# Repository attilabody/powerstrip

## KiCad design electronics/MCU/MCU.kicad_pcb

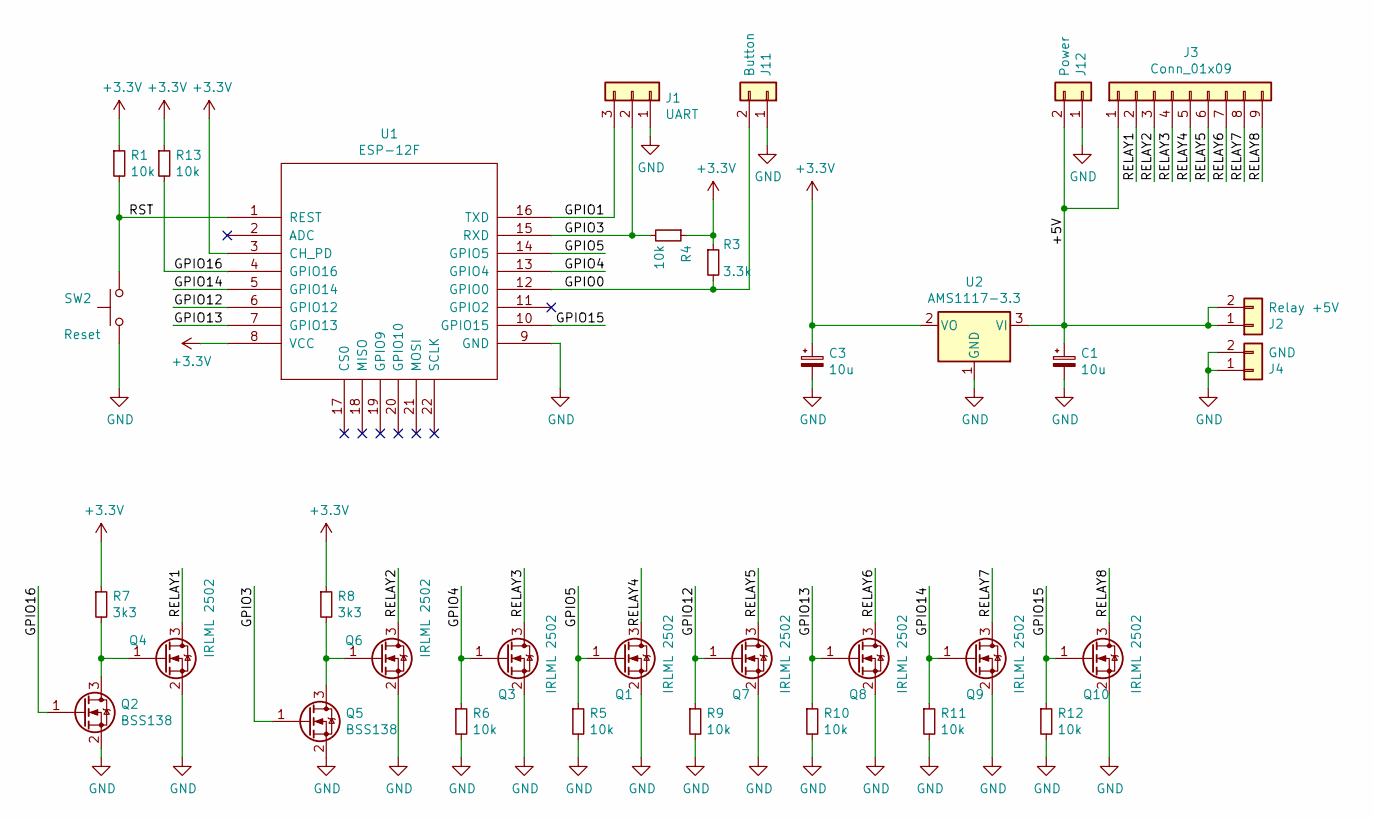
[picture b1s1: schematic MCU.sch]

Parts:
C1, C3: 10u; C_1206_3216Metric_Pad1.42x1.75mm_HandSolder
J1: UART; PinHeader_1x03_P2.54mm_Vertical
J2: Relay +5V; PinHeader_1x02_P2.54mm_Vertical
J3: Conn_01x09; PinHeader_1x09_P2.54mm_Vertical
J4: GND; PinHeader_1x02_P2.54mm_Vertical
J11: Button; JST_EH_B2B-EH-A_1x02_P2.50mm_Vertical
J12: Power; JST_EH_B2B-EH-A_1x02_P2.50mm_Vertical
Q1, Q3, Q4, Q6, Q7, Q8, Q9, Q10: IRLML 2502; SOT-23_Handsoldering
Q2, Q5: BSS138; SOT-23_Handsoldering
R1, R4, R5, R6, R9, R10, R11, R12, R13: 10k; R_0603_1608Metric_Pad1.05x0.95mm_HandSolder
R3: 3.3k; R_0603_1608Metric_Pad1.05x0.95mm_HandSolder
R7, R8: 3k3; R_0603_1608Metric_Pad1.05x0.95mm_HandSolder
SW2: Reset; SW_SPST_SKQG_WithStem
U1: ESP-12F; ESP-12E_SMD
U2: AMS1117-3.3; SOT-223-3_TabPin2

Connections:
+3V3: C3.1, R1.1, R3.1, R4.1, R7.1, R8.1, R13.1, U1.3 (CH_PD), U1.8 (VCC), U2.2 (VO)
/+5V: C1.1, J2.1, J2.2, J3.1, J12.2, U2.3 (VI); also elsewhere on the board
/GPIO0: J11.2, R3.2, U1.12 (GPIO0)
/GPIO1: J1.3, U1.16 (TXD)
/GPIO3: J1.2, Q5.1 (G), R4.2, U1.15 (RXD)
/GPIO4: Q3.1 (G), R6.1, U1.13 (GPIO4)
/GPIO5: Q1.1 (G), R5.1, U1.14 (GPIO5)
/GPIO12: Q7.1 (G), R9.1, U1.6 (GPIO12)
/GPIO13: Q8.1 (G), R10.1, U1.7 (GPIO13)
/GPIO14: Q9.1 (G), R11.1, U1.5 (GPIO14)
/GPIO15: Q10.1 (G), R12.1, U1.10 (GPIO15)
/GPIO16: Q2.1 (G), R13.2, U1.4 (GPIO16)
/RELAY1: J3.2, Q4.3 (D)
/RELAY2: J3.3, Q6.3 (D)
/RELAY3: J3.4, Q3.3 (D)
/RELAY4: J3.5, Q1.3 (D)
/RELAY5: J3.6, Q7.3 (D)
/RELAY6: J3.7, Q8.3 (D)
/RELAY7: J3.8, Q9.3 (D)
/RELAY8: J3.9, Q10.3 (D)
/RST: R1.2, SW2.1, U1.1 (REST)
GND: C1.2, C3.2, J1.1, J4.1, J4.2, J11.1, J12.1, Q1.2 (S), Q2.2 (S), Q3.2 (S), Q4.2 (S), Q5.2 (S), Q6.2 (S), Q7.2 (S), Q8.2 (S), Q9.2 (S), Q10.2 (S), R5.2, R6.2, R9.2, R10.2, R11.2, R12.2, SW2.2, U1.9 (GND), U2.1 (GND); also elsewhere on the board
unnamed: Q2.3 (D), Q4.1 (G), R7.2
unnamed: Q5.3 (D), Q6.1 (G), R8.2

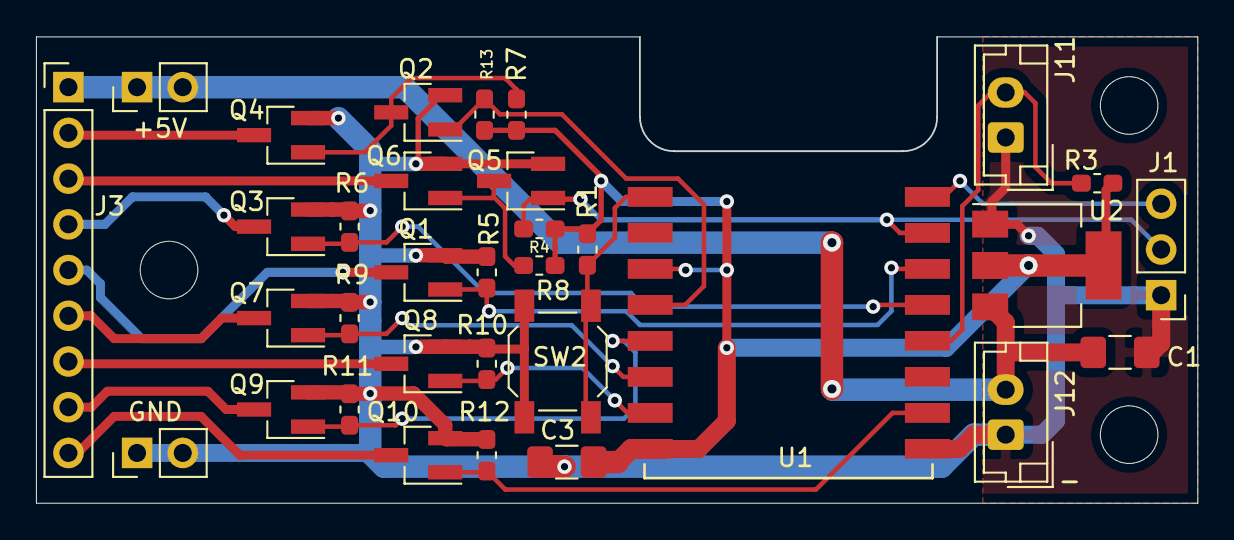
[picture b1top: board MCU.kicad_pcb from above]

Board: 2 copper layers, 64.5 x 25.9 mm, 33 parts (0 on the bottom side), 24 nets.

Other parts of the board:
+5V: Relay +5V; PinHeader_1x02_P2.54mm_Vertical
GND: GND; PinHeader_1x02_P2.54mm_Vertical

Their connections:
/+5V: +5V.1, +5V.2; also elsewhere on the board
GND: GND.1, GND.2; also elsewhere on the board

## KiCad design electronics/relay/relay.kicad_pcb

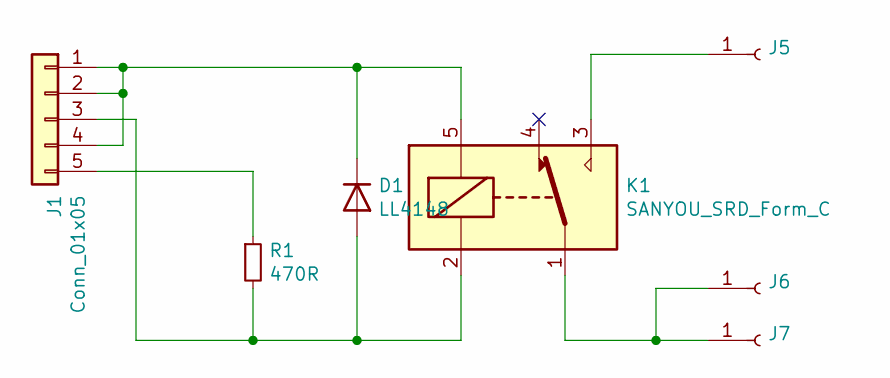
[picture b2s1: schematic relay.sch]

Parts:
D1: LL4148; D_MiniMELF
J1: Conn_01x05; PinHeader_1x05_P2.54mm_Vertical
J5, J6, J7: Conn_01x01_Female; SolderWire-Mains
K1: SANYOU_SRD_Form_C; Relay_SPDT_SANYOU_SRD_Series_Form_C
R1: 470R; R_0603_1608Metric_Pad0.98x0.95mm_HandSolder

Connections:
unnamed: D1.1 (K), J1.1, J1.2, J1.4, K1.5
unnamed: D1.2 (A), J1.3, K1.2, R1.2
unnamed: J1.5, R1.1
unnamed: J5.1, K1.3
unnamed: J6.1, J7.1, K1.1

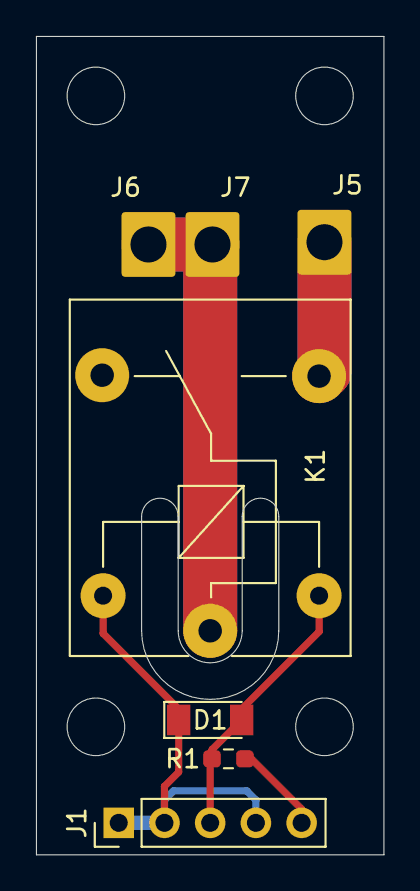
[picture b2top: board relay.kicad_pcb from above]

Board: 2 copper layers, 19.3 x 45.5 mm, 7 parts (0 on the bottom side), 5 nets.

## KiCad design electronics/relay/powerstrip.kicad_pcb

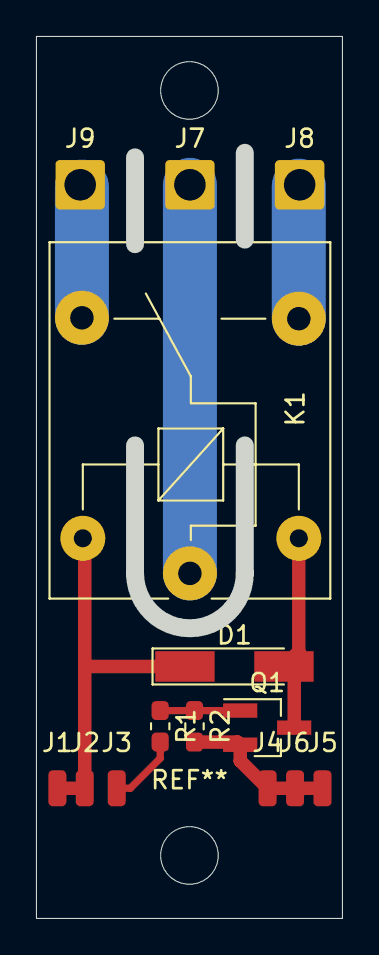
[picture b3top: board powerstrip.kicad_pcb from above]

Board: 2 copper layers, 16.1 x 48.1 mm, 14 parts (0 on the bottom side), 8 nets.

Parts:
D1: LL4148; D_MiniMELF_Handsoldering
J1, J2, J3, J4, J5, J6: Conn_01x01_Female; SolderWirePad_1x01_SMD_1x2mm
J7, J8, J9: Conn_01x01_Female; SolderWire-1sqmm_1x01_D1.4mm_OD2.7mm
K1: SANYOU_SRD_Form_C; Relay_SPDT_SANYOU_SRD_Series_Form_C
Q1: Q_NMOS_GSD; SOT-23_Handsoldering
R1, R2: R_Small; R_0603_1608Metric_Pad1.05x0.95mm_HandSolder

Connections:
GND: J4.1, J5.1, J6.1, Q1.2, R2.2
unnamed: D1.1, J1.1, J2.1, K1.5
unnamed: D1.2, K1.2, Q1.3
unnamed: J3.1, R1.2
unnamed: J7.1, K1.1
unnamed: J8.1, K1.3
unnamed: J9.1, K1.4
unnamed: Q1.1, R1.1, R2.1

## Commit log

2021-04-12 Relay unit 1st iteration
2021-04-12 kicad project renamed
2021-04-12 git subrepo clone (merge) https://github.com/jdunmire/kicad-ESP8266.git electronics/kicad-ESP8266
    subrepo:
    subdir: "electronics/kicad-ESP8266"
    merged: "1f3d2c6"
    upstream:
    origin: "https://github.com/jdunmire/kicad-ESP8266.git"
    branch: "master"
2021-04-14 ESP8266 board design ready
2021-04-18 Relay board ready, ESP3266 redesign (GPIO16 instead of GPIO0)
2021-04-19 MCU: GPIO3 instead if GPIO2
2021-04-19 Small PCB modifications, esphome config added
2021-04-20 MCU: removed pullup from CH_PD (direct 3.3V) improved clearance around the antenna added FreeCad design for case (uncompressed)
2021-05-16 PCB 1st batch
2021-05-16 Socket case for another socket type
2021-05-19 Housing: different caddys for the two supported socket versions
2021-05-19 PCB: parts moved a bit away from the JST connectors
2021-05-27 Top lock V2
2021-05-28 Multi shell units
2021-05-29 LED hole moved
2021-05-30 PCB rotated by 180 degrees
2021-06-01 Rotated PCB was not a good idea after all Added hager holes on the back
2021-06-06 Housing: Electronics segment
